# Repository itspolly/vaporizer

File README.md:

# Vaporizer

Open source Vaporizer KiCad schematics (requires DIY PCB layout, would love it if someone contributed a laid out PCB but there's no expectation of that here!)

Built using AI: one thing you might want to note is the 4mm traces for the HighCurrent netclass: such wide traces can probably be avoided if you design the traces with the volume of the trace in mind (printing 2oz copper will help) and will need to be avoided (necked) when connecting to IC pins due to limited clearance. Currently designed for a peak coil current of 5.0A.

See required libs here: https://github.com/itspolly/kicad-libs-vape.

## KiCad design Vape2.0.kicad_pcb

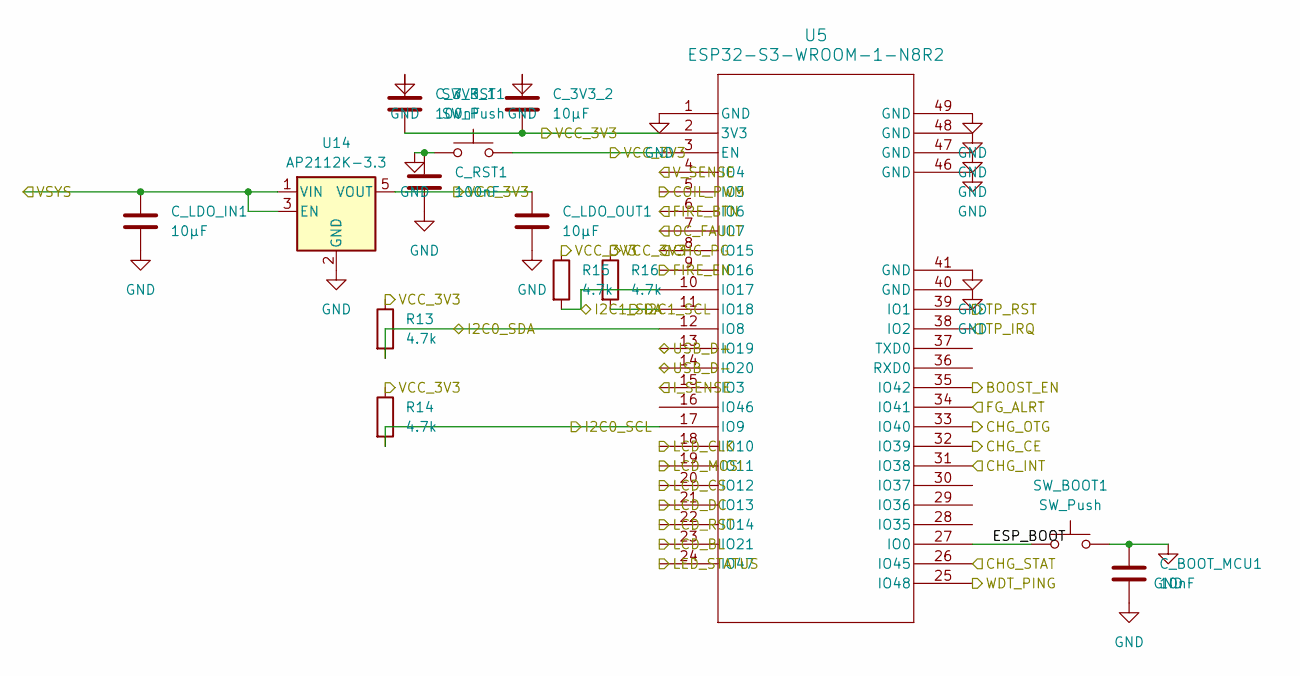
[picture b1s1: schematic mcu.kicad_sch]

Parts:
C_3V3_1: 100nF; C_0402_1005Metric
C_3V3_2: 10µF; C_0805_2012Metric
C_BOOT_MCU1: 10nF; C_0402_1005Metric
C_LDO_IN1: 10µF; C_0805_2012Metric
C_LDO_OUT1: 10µF; C_0805_2012Metric
C_RST1: 100nF; SW_SPST_TL3342
R13, R14, R15, R16: 4.7k; R_0402_1005Metric
SW_BOOT1: SW_Push; SW_SPST_TL3342
SW_RST1: SW_Push; SW_SPST_TL3342
U5: ESP32-S3-WROOM-1-N8R2; ESP32-S3-WROOM-1
U14: AP2112K-3.3; SOT-23-5

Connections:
/UI/FIRE_BTN: U5.6 (IO6); also elsewhere on the board
/UI/I2C0_SCL: R14.2, U5.17 (IO9); also elsewhere on the board
/UI/I2C0_SDA: R13.2, U5.12 (IO8); also elsewhere on the board
/UI/LCD_BL: U5.23 (IO21); also elsewhere on the board
/UI/LCD_CLK: U5.18 (IO10); also elsewhere on the board
/UI/LCD_CS: U5.20 (IO12); also elsewhere on the board
/UI/LCD_DC: U5.21 (IO13); also elsewhere on the board
/UI/LCD_MOSI: U5.19 (IO11); also elsewhere on the board
/UI/LCD_RST: U5.22 (IO14); also elsewhere on the board
/UI/LED_STATUS: U5.24 (IO47); also elsewhere on the board
/UI/TP_IRQ: U5.38 (IO2); also elsewhere on the board
/UI/TP_RST: U5.39 (IO1); also elsewhere on the board
/UI/VCC_3V3: C_3V3_1.2, C_3V3_2.2, C_LDO_OUT1.1, R13.1, R14.1, R15.1, R16.1, SW_RST1.2, U5.2 (3V3), U5.3 (EN), U14.5 (VOUT); also elsewhere on the board
/battery_management/CHG_CE: U5.32 (IO39); also elsewhere on the board
/battery_management/CHG_INT: U5.31 (IO38); also elsewhere on the board
/battery_management/CHG_OTG: U5.33 (IO40); also elsewhere on the board
/battery_management/CHG_PG: U5.8 (IO15); also elsewhere on the board
/battery_management/CHG_STAT: U5.26 (IO45); also elsewhere on the board
/battery_management/I2C1_SCL: R16.2, U5.11 (IO18); also elsewhere on the board
/battery_management/I2C1_SDA: R15.2, U5.10 (IO17); also elsewhere on the board
/battery_management/VSYS: C_LDO_IN1.1, U14.1 (VIN), U14.3 (EN); also elsewhere on the board
/boost_converter/BOOST_EN: U5.35 (IO42); also elsewhere on the board
/boost_converter/V_SENSE: U5.4 (IO4); also elsewhere on the board
/coil_driver/COIL_PWM: U5.5 (IO5); also elsewhere on the board
/coil_driver/I_SENSE: U5.15 (IO3); also elsewhere on the board
/coil_driver/OC_FAULT: U5.7 (IO7); also elsewhere on the board
/fuel_gauge/FG_ALRT: U5.34 (IO41); also elsewhere on the board
/mcu/ESP_BOOT: SW_BOOT1.1, U5.27 (IO0)
/mcu/FIRE_EN: U5.9 (IO16); also elsewhere on the board
/mcu/USB_D+: U5.13 (IO19); also elsewhere on the board
/mcu/USB_D-: U5.14 (IO20); also elsewhere on the board
/mcu/WDT_PING: U5.25 (IO48); also elsewhere on the board
GND: C_3V3_1.1, C_3V3_2.1, C_BOOT_MCU1.1, C_BOOT_MCU1.2, C_LDO_IN1.2, C_LDO_OUT1.2, C_RST1.1, C_RST1.2, SW_BOOT1.2, SW_RST1.1, U5.1 (GND), U5.40 (GND), U5.41 (GND), U5.46 (GND), U5.47 (GND), U5.48 (GND), U5.49 (GND), U14.2 (GND); also elsewhere on the board

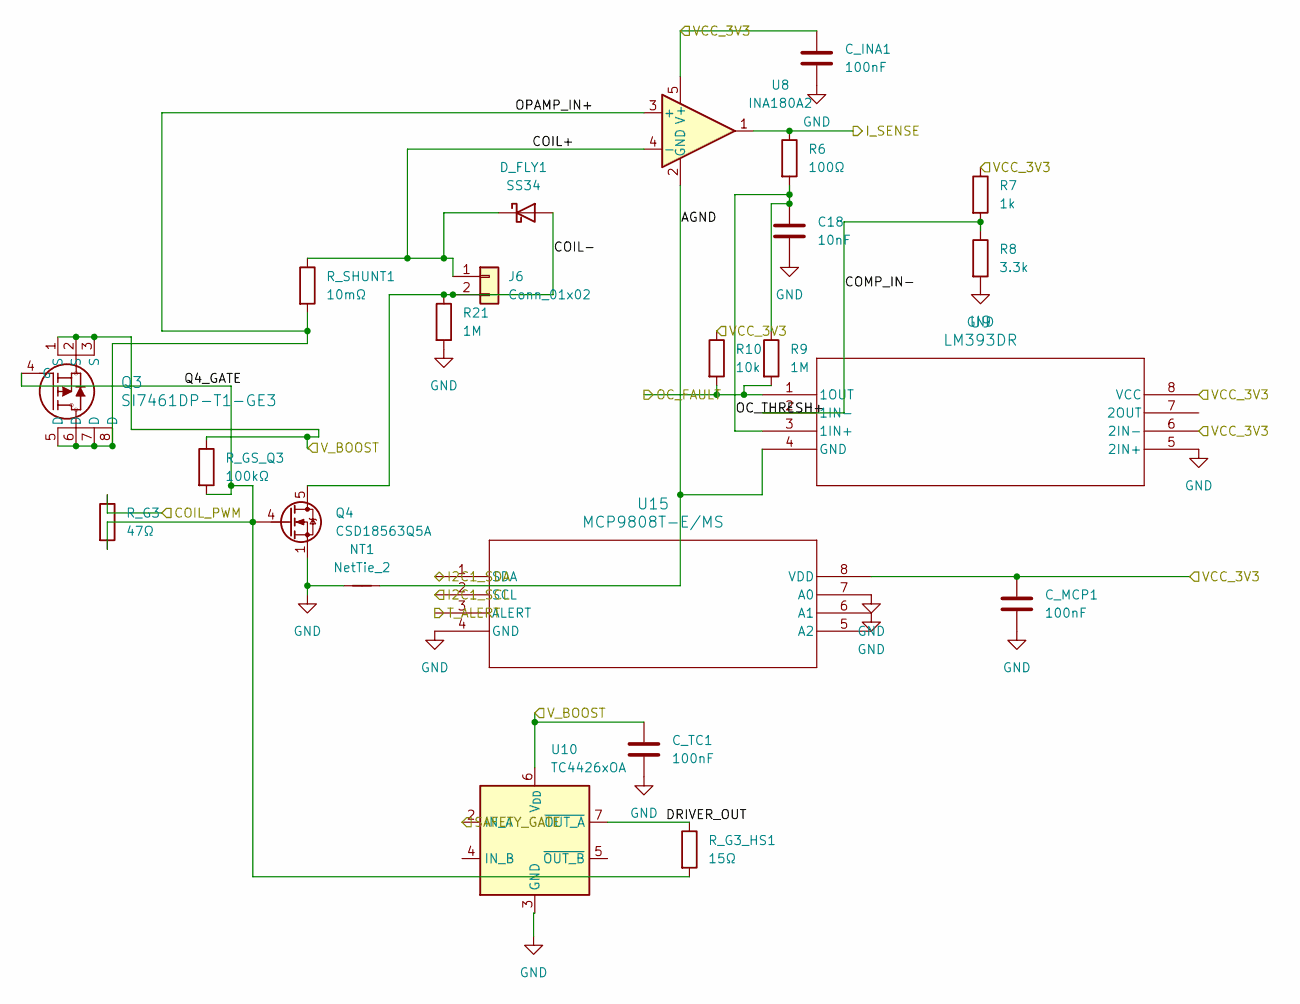
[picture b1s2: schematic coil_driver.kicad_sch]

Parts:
C18: 10nF; C_0402_1005Metric
C_INA1: 100nF; C_0402_1005Metric
C_MCP1: 100nF; C_0402_1005Metric
C_TC1: 100nF; C_0402_1005Metric
D_FLY1: SS34; D_SMA
J6: Conn_01x02; SolderWire-2.5sqmm_1x02_P8.8mm_D2.4mm_OD4.4mm
NT1: NetTie_2; NetTie-2_SMD_Pad0.5mm
Q3: SI7461DP-T1-GE3; PowerPAK_SO-8_Single
Q4: CSD18563Q5A; TDSON-8-1
R6: 100Ω; R_0402_1005Metric
R7: 1k; R_0402_1005Metric
R8: 3.3k; R_0402_1005Metric
R9, R21: 1M; R_0603_1608Metric
R10: 10k; R_0402_1005Metric
R_G3: 47Ω; R_0402_1005Metric
R_G3_HS1: 15Ω; R_0402_1005Metric
R_GS_Q3: 100kΩ; R_0402_1005Metric
R_SHUNT1: 10mΩ; R_2512_6332Metric
U8: INA180A2; SOT-23-5
U9: LM393DR; SOIC-8_3.9x4.9mm_P1.27mm
U10: TC4426xOA; SOIC-8_3.9x4.9mm_P1.27mm
U15: MCP9808T-E/MS; MSOP-8_3x3mm_P0.65mm

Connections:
/UI/VCC_3V3: C_INA1.1, C_MCP1.1, R7.1, R10.1, U8.5 (V+), U9.6 (2IN-), U9.8 (VCC), U15.8 (VDD); also elsewhere on the board
/battery_management/I2C1_SCL: U15.2 (SCL); also elsewhere on the board
/battery_management/I2C1_SDA: U15.1 (SDA); also elsewhere on the board
/boost_converter/V_BOOST: C_TC1.1, Q3.1 (S), Q3.2 (S), Q3.3 (S), R_GS_Q3.1, U10.6 (V_{DD}); also elsewhere on the board
/coil_driver/AGND: NT1.2, U8.2 (GND), U9.4 (GND)
/coil_driver/COIL+: D_FLY1.1 (K), J6.1, R_SHUNT1.1, U8.4 (-)
/coil_driver/COIL-: D_FLY1.2 (A), J6.2, Q4.5 (D), R21.1
/coil_driver/COIL_PWM: R_G3.1; also elsewhere on the board
/coil_driver/COMP_IN-: R7.2, R8.1, U9.2 (1IN-)
/coil_driver/DRIVER_OUT: R_G3_HS1.1, U10.7 (~OUT_A)
/coil_driver/I_SENSE: R6.1, U8.1; also elsewhere on the board
/coil_driver/OC_FAULT: R9.2, R10.2, U9.1 (1OUT); also elsewhere on the board
/coil_driver/OC_THRESH+: C18.1, R6.2, R9.1, U9.3 (1IN+)
/coil_driver/OPAMP_IN+: Q3.5 (D), Q3.6 (D), Q3.7 (D), Q3.8 (D), R_SHUNT1.2, U8.3 (+)
/coil_driver/Q4_GATE: Q3.4 (G), Q4.4 (G), R_G3.2, R_G3_HS1.2, R_GS_Q3.2
/coil_driver/SAFETY_GATE: U10.2 (IN_A); also elsewhere on the board
/coil_driver/T_ALERT: U15.3 (ALERT); also elsewhere on the board
GND: C18.2, C_INA1.2, C_MCP1.2, C_TC1.2, NT1.1, Q4.1 (S), Q4.2 (S), Q4.3 (S), R8.2, R21.2, U9.5 (2IN+), U10.3 (GND), U15.4 (GND), U15.6 (A1), U15.7 (A0); also elsewhere on the board

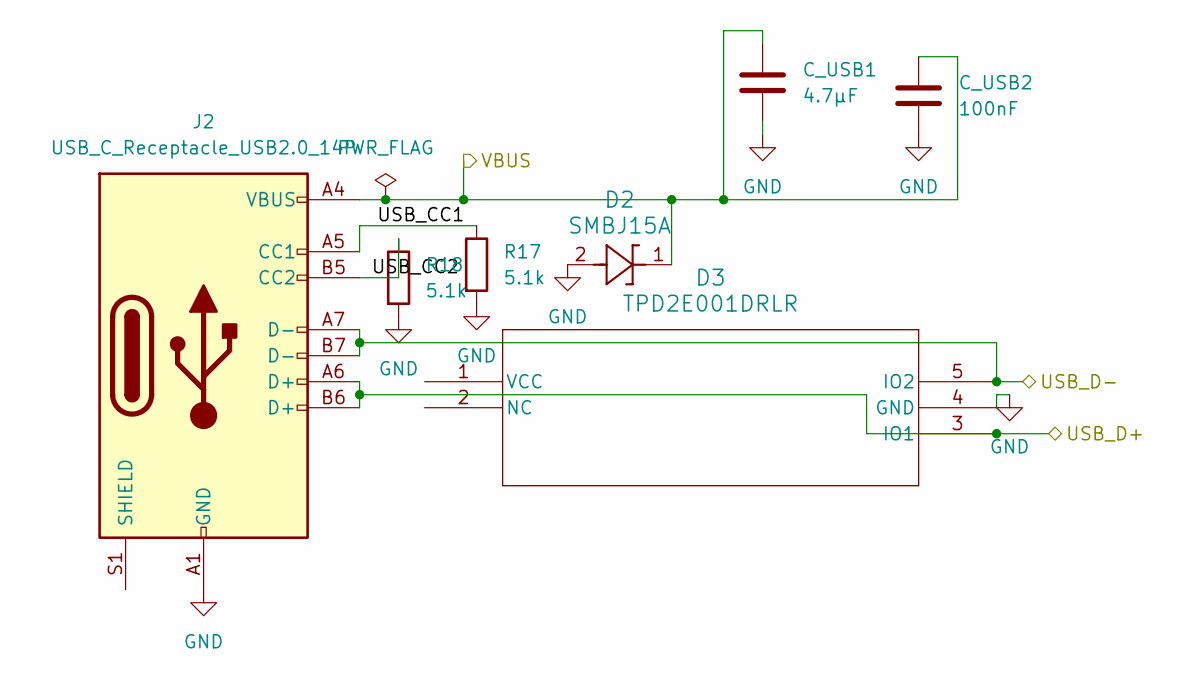
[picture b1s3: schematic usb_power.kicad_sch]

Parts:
C_USB1: 4.7µF; C_0805_2012Metric
C_USB2: 100nF; C_0402_1005Metric
D2: SMBJ15A; D_SMB
D3: TPD2E001DRLR; SOT-23-5
J2: USB_C_Receptacle_USB2.0_14P; USB_C_Receptacle_GCT_USB4110
R17, R18: 5.1k; R_0402_1005Metric

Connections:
/battery_management/VBUS: C_USB1.1, C_USB2.1, D2.1, J2.A4 (VBUS), J2.A9 (VBUS), J2.B4 (VBUS), J2.B9 (VBUS); also elsewhere on the board
/mcu/USB_D+: D3.3 (IO1), J2.A6 (D+), J2.B6 (D+); also elsewhere on the board
/mcu/USB_D-: D3.5 (IO2), J2.A7 (D-), J2.B7 (D-); also elsewhere on the board
/usb_power/USB_CC1: J2.A5 (CC1), R17.1
/usb_power/USB_CC2: J2.B5 (CC2), R18.1
GND: C_USB1.2, C_USB2.2, D2.2, D3.4 (GND), J2.A1 (GND), J2.A12 (GND), J2.B1 (GND), J2.B12 (GND), R17.2, R18.2; also elsewhere on the board

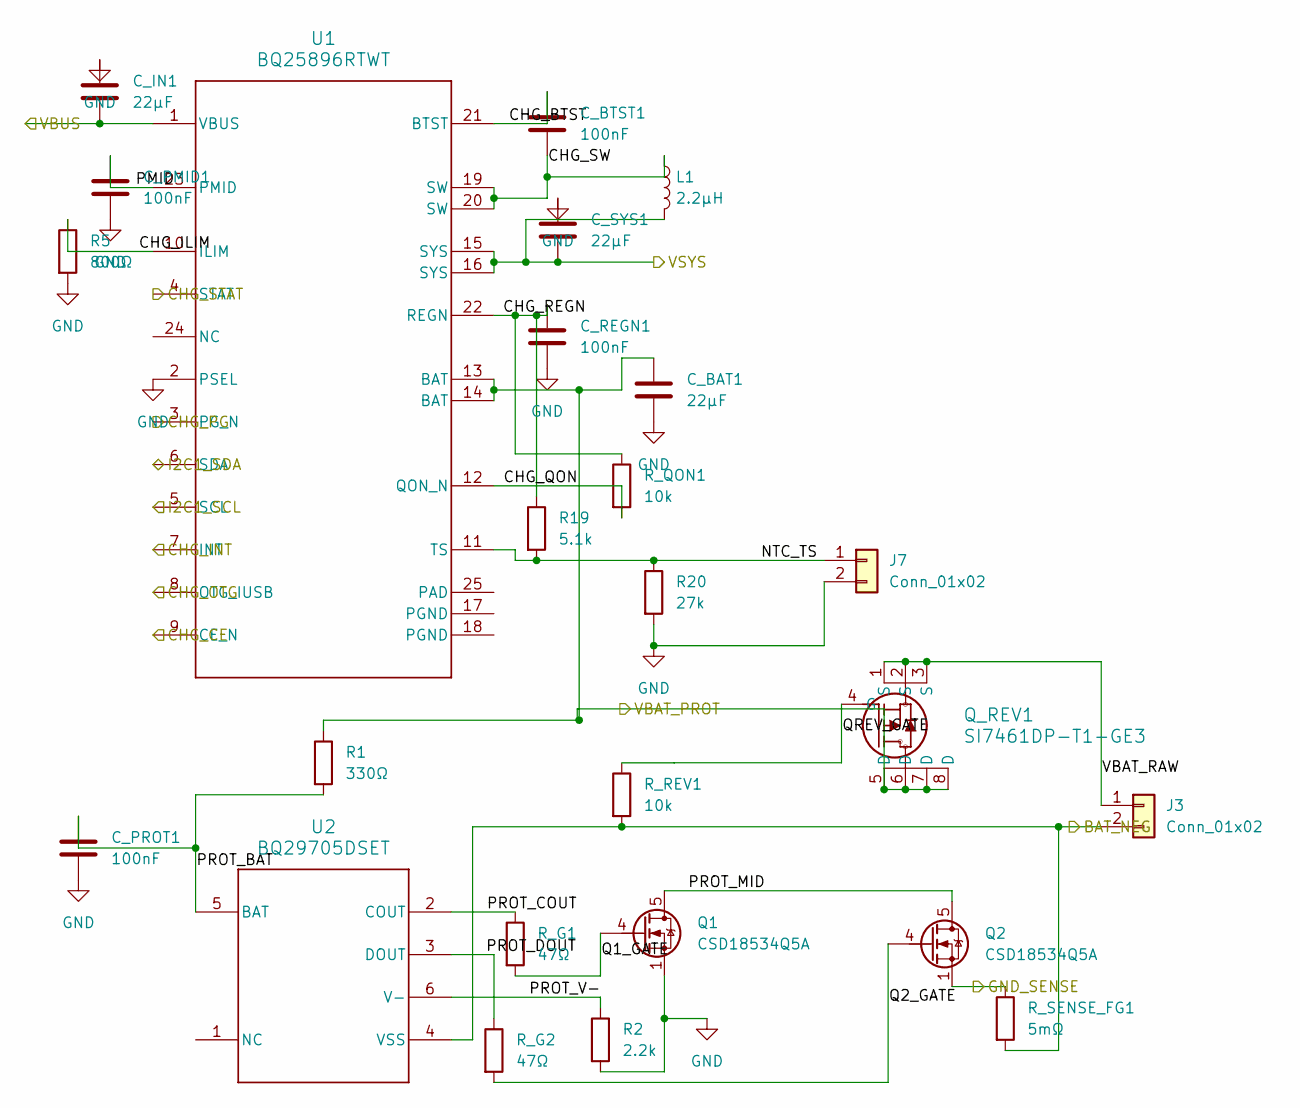
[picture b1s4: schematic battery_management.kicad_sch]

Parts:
C_BAT1: 22µF; C_0805_2012Metric
C_BTST1: 100nF; C_0402_1005Metric
C_IN1: 22µF; C_0805_2012Metric
C_PMID1: 100nF; C_0402_1005Metric
C_PROT1: 100nF; C_0402_1005Metric
C_REGN1: 100nF; C_0402_1005Metric
C_SYS1: 22µF; C_0805_2012Metric
J3: Conn_01x02; SolderWire-2.5sqmm_1x02_P8.8mm_D2.4mm_OD4.4mm
J7: Conn_01x02; SolderWire-0.5sqmm_1x02_P4.6mm_D0.9mm_OD2.1mm
L1: 2.2µH; L_7.3x7.3_H3.5
Q1, Q2: CSD18534Q5A; TDSON-8-1
Q_REV1: SI7461DP-T1-GE3; PowerPAK_SO-8_Single
R1: 330Ω; R_0402_1005Metric
R2: 2.2k; R_0402_1005Metric
R5: 800Ω; R_0402_1005Metric
R19: 5.1k; R_0402_1005Metric
R20: 27k; R_0402_1005Metric
R_G1, R_G2: 47Ω; R_0402_1005Metric
R_QON1: 10k; R_0402_1005Metric
R_REV1: 10k; R_0402_1005Metric
R_SENSE_FG1: 5mΩ; R_2512_6332Metric
U1: BQ25896RTWT; Texas_RTW_WQFN-24-1EP_4x4mm_P0.5mm_EP2.7x2.7mm_ThermalVias
U2: BQ29705DSET; SON50P150X150X80-6N

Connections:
/battery_management/BAT_NEG: J3.2, R_REV1.2, R_SENSE_FG1.2, U2.4 (VSS); also elsewhere on the board
/battery_management/CHG_BTST: C_BTST1.1, U1.21 (BTST)
/battery_management/CHG_CE: U1.9 (CE_N); also elsewhere on the board
/battery_management/CHG_ILIM: R5.1, U1.10 (ILIM)
/battery_management/CHG_INT: U1.7 (INT); also elsewhere on the board
/battery_management/CHG_OTG: U1.8 (OTG_IUSB); also elsewhere on the board
/battery_management/CHG_PG: U1.3 (PG_N); also elsewhere on the board
/battery_management/CHG_QON: R_QON1.2, U1.12 (QON_N)
/battery_management/CHG_REGN: C_REGN1.1, R19.1, R_QON1.1, U1.22 (REGN)
/battery_management/CHG_STAT: U1.4 (STAT); also elsewhere on the board
/battery_management/CHG_SW: C_BTST1.2, L1.1, U1.19 (SW), U1.20 (SW)
/battery_management/GND_SENSE: Q2.1 (S), Q2.2 (S), Q2.3 (S), R_SENSE_FG1.1; also elsewhere on the board
/battery_management/I2C1_SCL: U1.5 (SCL); also elsewhere on the board
/battery_management/I2C1_SDA: U1.6 (SDA); also elsewhere on the board
/battery_management/NTC_TS: J7.1, R19.2, R20.1, U1.11 (TS)
/battery_management/PMID: C_PMID1.1, U1.23 (PMID)
/battery_management/PROT_BAT: C_PROT1.1, R1.2, U2.5 (BAT)
/battery_management/PROT_COUT: R_G1.1, U2.2 (COUT)
/battery_management/PROT_DOUT: R_G2.1, U2.3 (DOUT)
/battery_management/PROT_MID: Q1.5 (D), Q2.5 (D)
/battery_management/PROT_V-: R2.1, U2.6 (V-)
/battery_management/Q1_GATE: Q1.4 (G), R_G1.2
/battery_management/Q2_GATE: Q2.4 (G), R_G2.2
/battery_management/QREV_GATE: Q_REV1.4 (G), R_REV1.1
/battery_management/VBAT_PROT: C_BAT1.1, Q_REV1.5 (D), Q_REV1.6 (D), Q_REV1.7 (D), Q_REV1.8 (D), R1.1, U1.13 (BAT), U1.14 (BAT); also elsewhere on the board
/battery_management/VBAT_RAW: J3.1, Q_REV1.1 (S), Q_REV1.2 (S), Q_REV1.3 (S)
/battery_management/VBUS: C_IN1.2, U1.1 (VBUS); also elsewhere on the board
/battery_management/VSYS: C_SYS1.2, L1.2, U1.15 (SYS), U1.16 (SYS); also elsewhere on the board
GND: C_BAT1.2, C_IN1.1, C_PMID1.2, C_PROT1.2, C_REGN1.2, C_SYS1.1, J7.2, Q1.1 (S), Q1.2 (S), Q1.3 (S), R2.2, R5.2, R20.2, U1.2 (PSEL); also elsewhere on the board

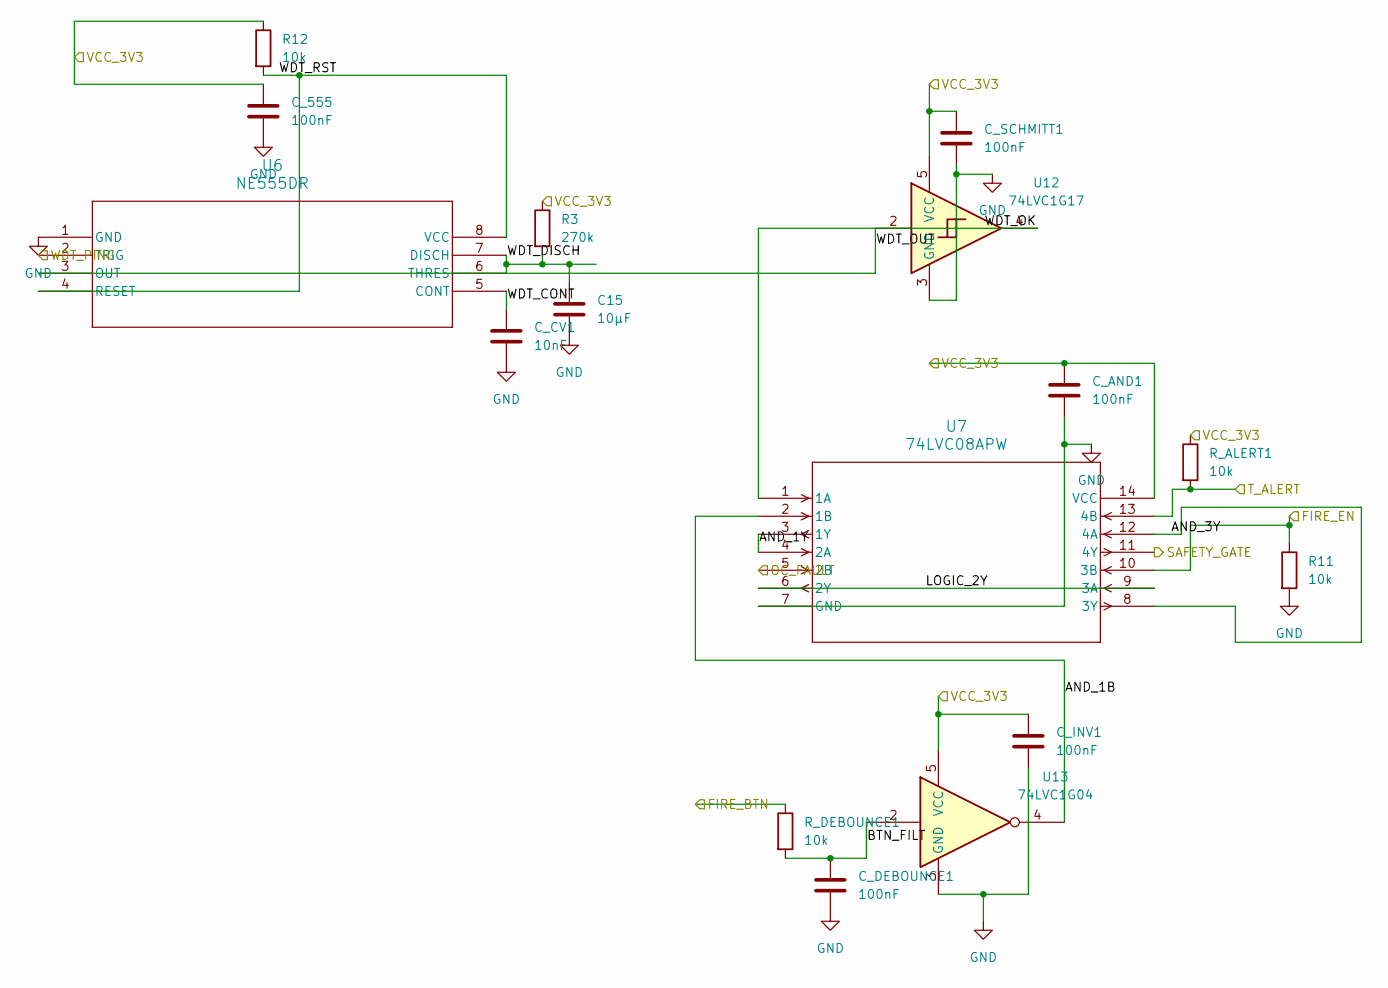
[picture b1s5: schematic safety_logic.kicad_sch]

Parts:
C15: 10µF; C_0805_2012Metric
C_555: 100nF; C_0402_1005Metric
C_AND1: 100nF; C_0402_1005Metric
C_CV1: 10nF; C_0402_1005Metric
C_DEBOUNCE1: 100nF; C_0402_1005Metric
C_INV1: 100nF; C_0402_1005Metric
C_SCHMITT1: 100nF; C_0402_1005Metric
R3: 270k; R_0603_1608Metric
R11, R12: 10k; R_0402_1005Metric
R_ALERT1: 10k; R_0402_1005Metric
R_DEBOUNCE1: 10k; R_0402_1005Metric
U6: NE555DR; SOIC-8_3.9x4.9mm_P1.27mm
U7: 74LVC08APW; TSSOP-14_4.4x5mm_P0.65mm
U12: 74LVC1G17; SOT-353_SC-70-5
U13: 74LVC1G04; SOT-353_SC-70-5

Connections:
/UI/FIRE_BTN: R_DEBOUNCE1.1; also elsewhere on the board
/UI/VCC_3V3: C_555.1, C_AND1.1, C_INV1.1, C_SCHMITT1.1, R3.1, R12.1, R_ALERT1.1, U7.14 (VCC), U12.5 (VCC), U13.5 (VCC); also elsewhere on the board
/coil_driver/OC_FAULT: U7.5 (2B); also elsewhere on the board
/coil_driver/SAFETY_GATE: U7.11 (4Y); also elsewhere on the board
/coil_driver/T_ALERT: R_ALERT1.2, U7.13 (4B); also elsewhere on the board
/mcu/FIRE_EN: R11.1, U7.10 (3B); also elsewhere on the board
/mcu/WDT_PING: U6.2 (TRIG); also elsewhere on the board
/safety_logic/AND_1B: U7.2 (1B), U13.4
/safety_logic/AND_1Y: U7.3 (1Y), U7.4 (2A)
/safety_logic/AND_3Y: U7.8 (3Y), U7.12 (4A)
/safety_logic/BTN_FILT: C_DEBOUNCE1.1, R_DEBOUNCE1.2, U13.2
/safety_logic/LOGIC_2Y: U7.6 (2Y), U7.9 (3A)
/safety_logic/WDT_CONT: C_CV1.1, U6.5 (CONT)
/safety_logic/WDT_DISCH: C15.1, R3.2, U6.6 (THRES), U6.7 (DISCH)
/safety_logic/WDT_OK: U7.1 (1A), U12.4
/safety_logic/WDT_OUT: U6.3 (OUT), U12.2
/safety_logic/WDT_RST: R12.2, U6.4 (RESET), U6.8 (VCC)
GND: C15.2, C_555.2, C_AND1.2, C_CV1.2, C_DEBOUNCE1.2, C_INV1.2, C_SCHMITT1.2, R11.2, U6.1 (GND), U7.7 (GND), U12.3 (GND), U13.3 (GND); also elsewhere on the board

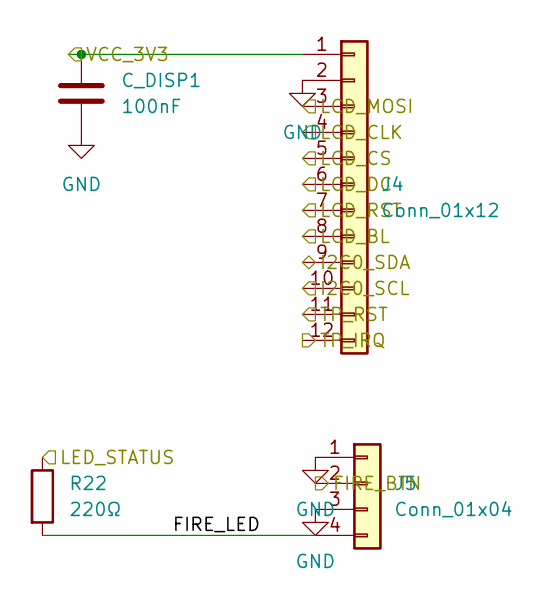
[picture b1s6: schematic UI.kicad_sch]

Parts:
C_DISP1: 100nF; C_0402_1005Metric
J4: Conn_01x12; JST_GH_SM12B-GHS-TB_1x12-1MP_P1.25mm_Horizontal
J5: Conn_01x04; JST_XH_B4B-XH-A_1x04_P2.50mm_Vertical
R22: 220Ω; R_0402_1005Metric

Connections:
/UI/FIRE_BTN: J5.2; also elsewhere on the board
/UI/FIRE_LED: J5.4, R22.2
/UI/I2C0_SCL: J4.10; also elsewhere on the board
/UI/I2C0_SDA: J4.9; also elsewhere on the board
/UI/LCD_BL: J4.8; also elsewhere on the board
/UI/LCD_CLK: J4.4; also elsewhere on the board
/UI/LCD_CS: J4.5; also elsewhere on the board
/UI/LCD_DC: J4.6; also elsewhere on the board
/UI/LCD_MOSI: J4.3; also elsewhere on the board
/UI/LCD_RST: J4.7; also elsewhere on the board
/UI/LED_STATUS: R22.1; also elsewhere on the board
/UI/TP_IRQ: J4.12; also elsewhere on the board
/UI/TP_RST: J4.11; also elsewhere on the board
/UI/VCC_3V3: C_DISP1.1, J4.1; also elsewhere on the board
GND: C_DISP1.2, J4.2, J5.1, J5.3; also elsewhere on the board

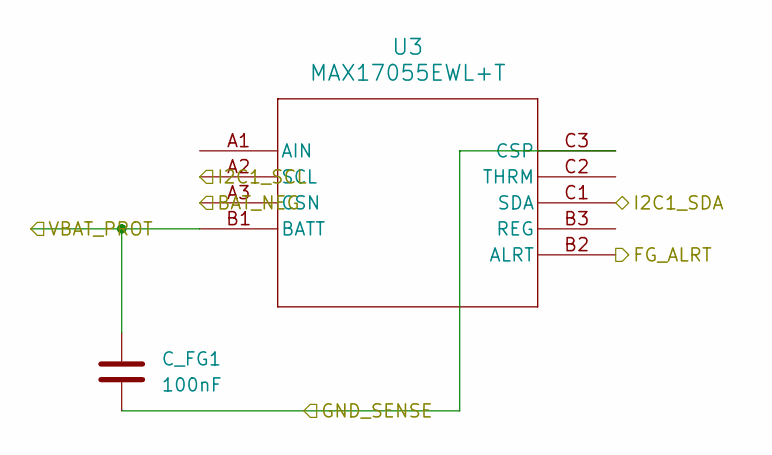
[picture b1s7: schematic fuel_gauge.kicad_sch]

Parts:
C_FG1: 100nF; C_0402_1005Metric
U3: MAX17055EWL+T; BGA9N40P3X3_140X149X69N

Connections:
/battery_management/BAT_NEG: U3.A3 (CSN); also elsewhere on the board
/battery_management/GND_SENSE: C_FG1.2, U3.C3 (CSP); also elsewhere on the board
/battery_management/I2C1_SCL: U3.A2 (SCL); also elsewhere on the board
/battery_management/I2C1_SDA: U3.C1 (SDA); also elsewhere on the board
/battery_management/VBAT_PROT: C_FG1.1, U3.B1 (BATT); also elsewhere on the board
/fuel_gauge/FG_ALRT: U3.B2 (ALRT); also elsewhere on the board

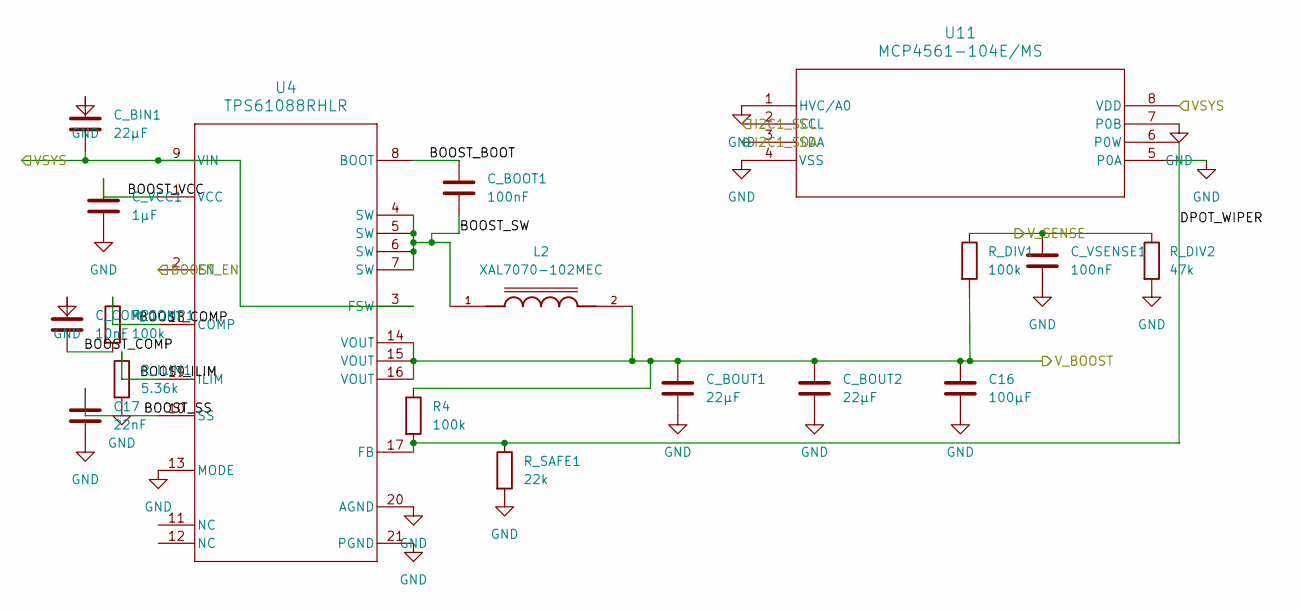
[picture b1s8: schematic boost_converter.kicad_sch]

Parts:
C16: 100µF; C_1206_3216Metric
C17: 22nF; C_0402_1005Metric
C_BIN1: 22µF; C_0805_2012Metric
C_BOOT1: 100nF; C_0402_1005Metric
C_BOUT1, C_BOUT2: 22µF; C_0805_2012Metric
C_COMP1: 10nF; C_0402_1005Metric
C_VCC1: 1µF; C_0402_1005Metric
C_VSENSE1: 100nF; C_0402_1005Metric
L2: XAL7070-102MEC; IND_XAL7070-102MEC; PARTREV 11/02/18
R4: 100k; R_0402_1005Metric
R_COMP1: 100k; R_0402_1005Metric
R_DIV1: 100k; R_0402_1005Metric
R_DIV2: 47k; R_0402_1005Metric
R_ILIM1: 5.36k; R_0402_1005Metric
R_SAFE1: 22k; R_0402_1005Metric
U4: TPS61088RHLR; QFN-20-1EP_4x4mm_P0.5mm_EP2.7x2.7mm_ThermalVias
U11: MCP4561-104E/MS; SOIC-8_3.9x4.9mm_P1.27mm

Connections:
/battery_management/I2C1_SCL: U11.2 (SCL); also elsewhere on the board
/battery_management/I2C1_SDA: U11.3 (SDA); also elsewhere on the board
/battery_management/VSYS: C_BIN1.2, U4.3 (FSW), U4.9 (VIN), U11.8 (VDD); also elsewhere on the board
/boost_converter/BOOST_BOOT: C_BOOT1.1, U4.8 (BOOT)
/boost_converter/BOOST_COMP: C_COMP1.2, R_COMP1.1, R_COMP1.2, U4.18 (COMP)
/boost_converter/BOOST_EN: U4.2 (EN); also elsewhere on the board
/boost_converter/BOOST_ILIM: R_ILIM1.1, U4.19 (ILIM)
/boost_converter/BOOST_SS: C17.1, U4.10 (SS)
/boost_converter/BOOST_SW: C_BOOT1.2, L2.1, U4.4 (SW), U4.5 (SW), U4.6 (SW), U4.7 (SW)
/boost_converter/BOOST_VCC: C_VCC1.1, U4.1 (VCC)
/boost_converter/DPOT_WIPER: R4.2, R_SAFE1.1, U4.17 (FB), U11.6 (P0W)
/boost_converter/V_BOOST: C16.1, C_BOUT1.1, C_BOUT2.1, L2.2, R4.1, R_DIV1.2, U4.14 (VOUT), U4.15 (VOUT), U4.16 (VOUT); also elsewhere on the board
/boost_converter/V_SENSE: C_VSENSE1.1, R_DIV1.1, R_DIV2.1; also elsewhere on the board
GND: C16.2, C17.2, C_BIN1.1, C_BOUT1.2, C_BOUT2.2, C_COMP1.1, C_VCC1.2, C_VSENSE1.2, R_DIV2.2, R_ILIM1.2, R_SAFE1.2, U4.13 (MODE), U4.20 (AGND), U4.21 (PGND), U11.1 (HVC/A0), U11.4 (VSS), U11.5 (P0A), U11.7 (P0B); also elsewhere on the board

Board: 2 copper layers, 109 parts (0 on the bottom side), 84 nets, no tracks yet.

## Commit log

2026-01-17 initial commit: root sheet status: Step 15: Wire Safety System Signals
2026-01-17 up to step 16 of root sheet wiring
2026-01-17 completed root sheet (aside from missing V_SENSE conn, pray to god claude summarised the rest of the steps right)
2026-01-17 finished schematics
2026-01-17 schematic pdf
2026-01-17 footprints
2026-01-18 fix missing connections, complete footprints
2026-01-18 fix oopsie
2026-01-18 remove extra connection
2026-01-18 net labels
2026-01-18 fixed labels
2026-01-18 net classes
2026-01-18 add missing footprints
2026-01-18 first pcb?
2026-01-18 configure netclasses for pcb
2026-01-19 change schematic netclasses
2026-01-20 cleanup wire
2026-01-20 place components
2026-01-20 readme
2026-01-20 Update README with required libraries link
    Added a note about required libraries for the project.
2026-01-20 Add Unlicense to LICENSE file
    Added the Unlicense text to the LICENSE file.
2026-01-20 Update README with peak coil current information
    Added note about peak coil current specification.
